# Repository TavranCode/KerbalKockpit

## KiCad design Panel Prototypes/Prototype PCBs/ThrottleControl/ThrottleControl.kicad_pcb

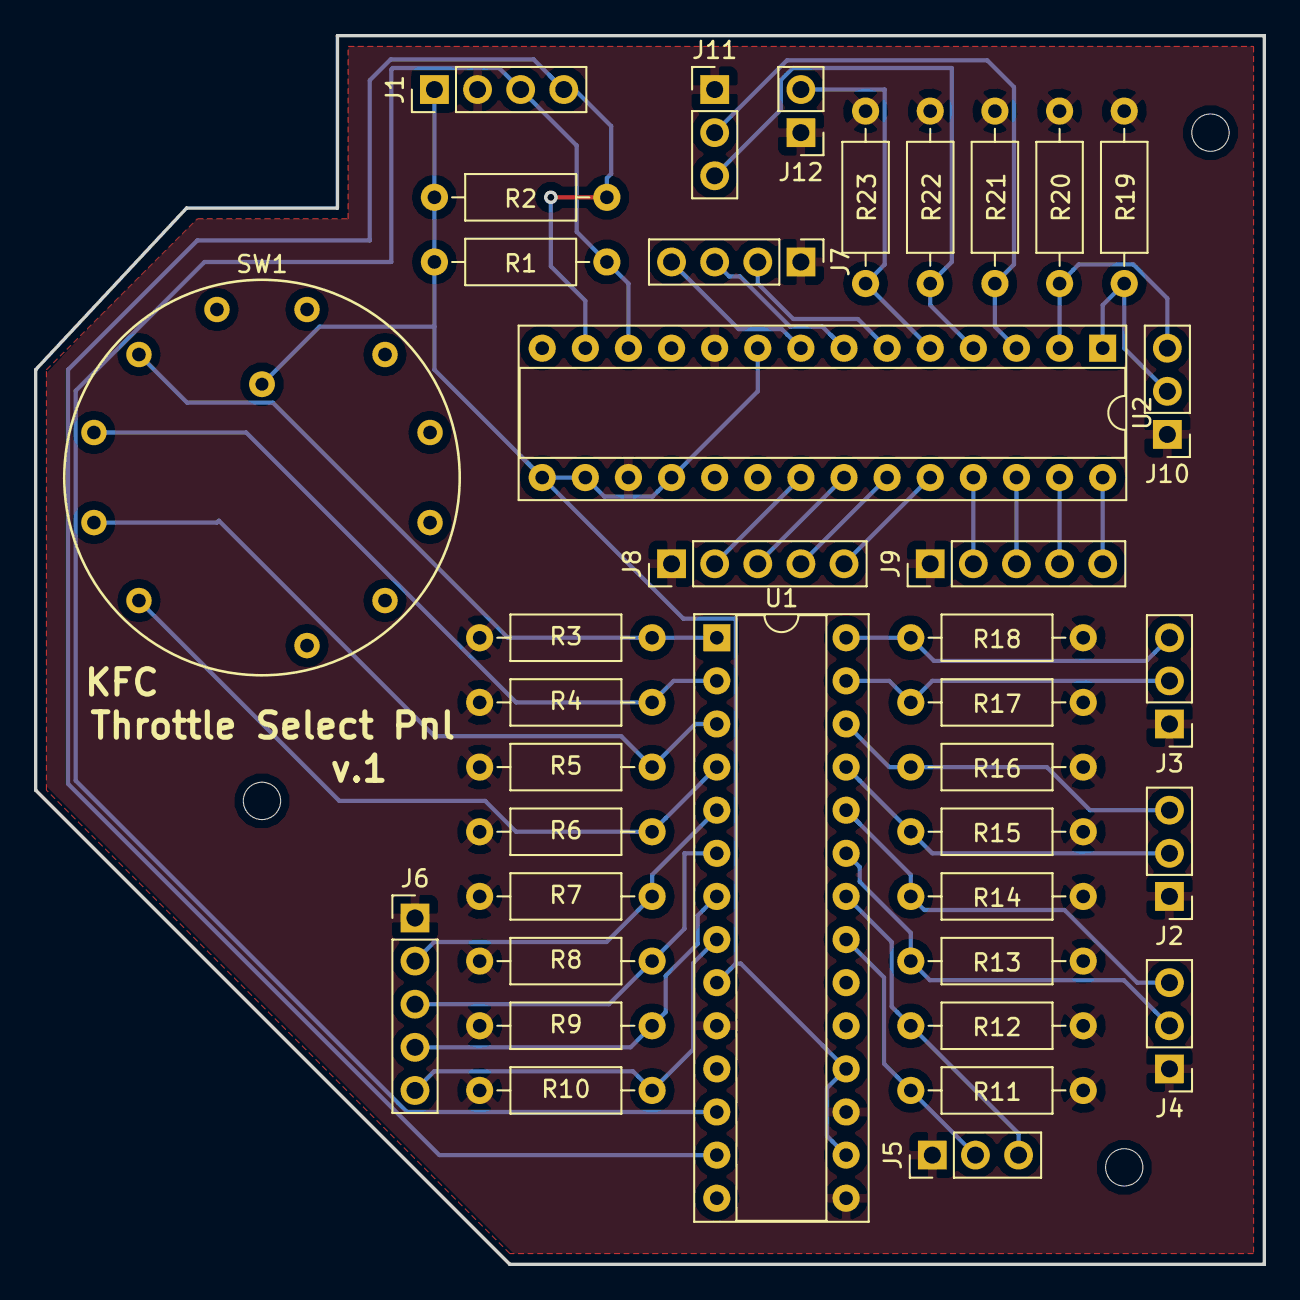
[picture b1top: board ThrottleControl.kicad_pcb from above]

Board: 2 copper layers, 72.4 x 72.4 mm, 38 parts (0 on the bottom side), 36 nets.

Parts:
J1: Conn_01x04; PinHeader_1x04_P2.54mm_Vertical
J2: Conn_Warp; PinHeader_1x03_P2.54mm_Vertical
J3: Conn_Pwarp; PinHeader_1x03_P2.54mm_Vertical
J4: Conn_CamZoom; PinHeader_1x03_P2.54mm_Vertical
J5: Conn_VelRot; PinHeader_1x03_P2.54mm_Vertical
J6: Conn_CamRot; PinHeader_1x05_P2.54mm_Vertical
J7: Conn_UNa; PinHeader_1x04_P2.54mm_Vertical
J8: Conn_UNb; PinHeader_1x05_P2.54mm_Vertical
J9: Conn_UNc; PinHeader_1x05_P2.54mm_Vertical
J10: Conn_MapBs; PinHeader_1x03_P2.54mm_Vertical
J11: Conn_VslSw; PinHeader_1x03_P2.54mm_Vertical
J12: Conn_WarpC; PinHeader_1x02_P2.54mm_Vertical
R1, R2, R3, R4, R5, R6, R7, R8, R9, R10, R11, R12, R13, R14, R15, R16, R17, R18, R19, R20, R21, R22, R23: 4.7k; R_Axial_DIN0207_L6.3mm_D2.5mm_P10.16mm_Horizontal
SW1: SW_Rotary12; R25_Rotary
U1, U2: MCP23017_SP; DIP-28_W7.62mm_Socket

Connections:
+5V: J1.1, R1.2, R2.2, SW1.13, U1.9, U1.16, U1.18, U2.9, U2.15, U2.16, U2.18
/CZ1: J4.2, R13.2, U1.23
/CZ2: J4.3, R14.2, U1.24
/Cam1: J6.2, R7.2, U1.5
/Cam2: J6.3, R8.2, U1.6
/Cam3: J6.4, R9.2, U1.7
/Cam4: J6.5, R10.2, U1.8
/Map: J10.3, R20.2, U2.2
/MpR: J10.2, R19.2, U2.1
/PWR1: J3.2, R17.2, U1.27
/PWR2: J3.3, R18.2, U1.28
/SCK: J1.3, R1.1, U1.12, U2.12
/SDA: J1.4, R2.1, U1.13, U2.13
/TH0: R6.2, SW1.1, U1.4
/TH25: R5.2, SW1.2, U1.3
/TH50: R4.2, SW1.3, U1.2
/TH75: R3.2, SW1.4, U1.1
/TSW1: J11.2, R21.2, U2.3
/TSW2: J11.3, R22.2, U2.4
/UNa1: J7.2, U2.6
/UNa2: J7.3, U2.7
/UNa3: J7.4, U2.8
/UNb1: J8.2, U2.21
/UNb2: J8.3, U2.22
/UNb3: J8.4, U2.23
/UNb4: J8.5, U2.24
/UNc1: J9.2, U2.25
/UNc2: J9.3, U2.26
/UNc3: J9.4, U2.27
/UNc4: J9.5, U2.28
/VOR: J5.2, R11.2, U1.21
/VTR: J5.3, R12.2, U1.22
/WPC: J12.2, R23.2, U2.5
/WRP1: J2.2, R15.2, U1.25
/WRP2: J2.3, R16.2, U1.26
Earth: J1.2, J2.1, J3.1, J4.1, J5.1, J6.1, J7.1, J8.1, J9.1, J10.1, J11.1, J12.1, R3.1, R4.1, R5.1, R6.1, R7.1, R8.1, R9.1, R10.1, R11.1, R12.1, R13.1, R14.1, R15.1, R16.1, R17.1, R18.1, R19.1, R20.1, R21.1, R22.1, R23.1, U1.10, U1.15, U1.17, U2.10, U2.17
